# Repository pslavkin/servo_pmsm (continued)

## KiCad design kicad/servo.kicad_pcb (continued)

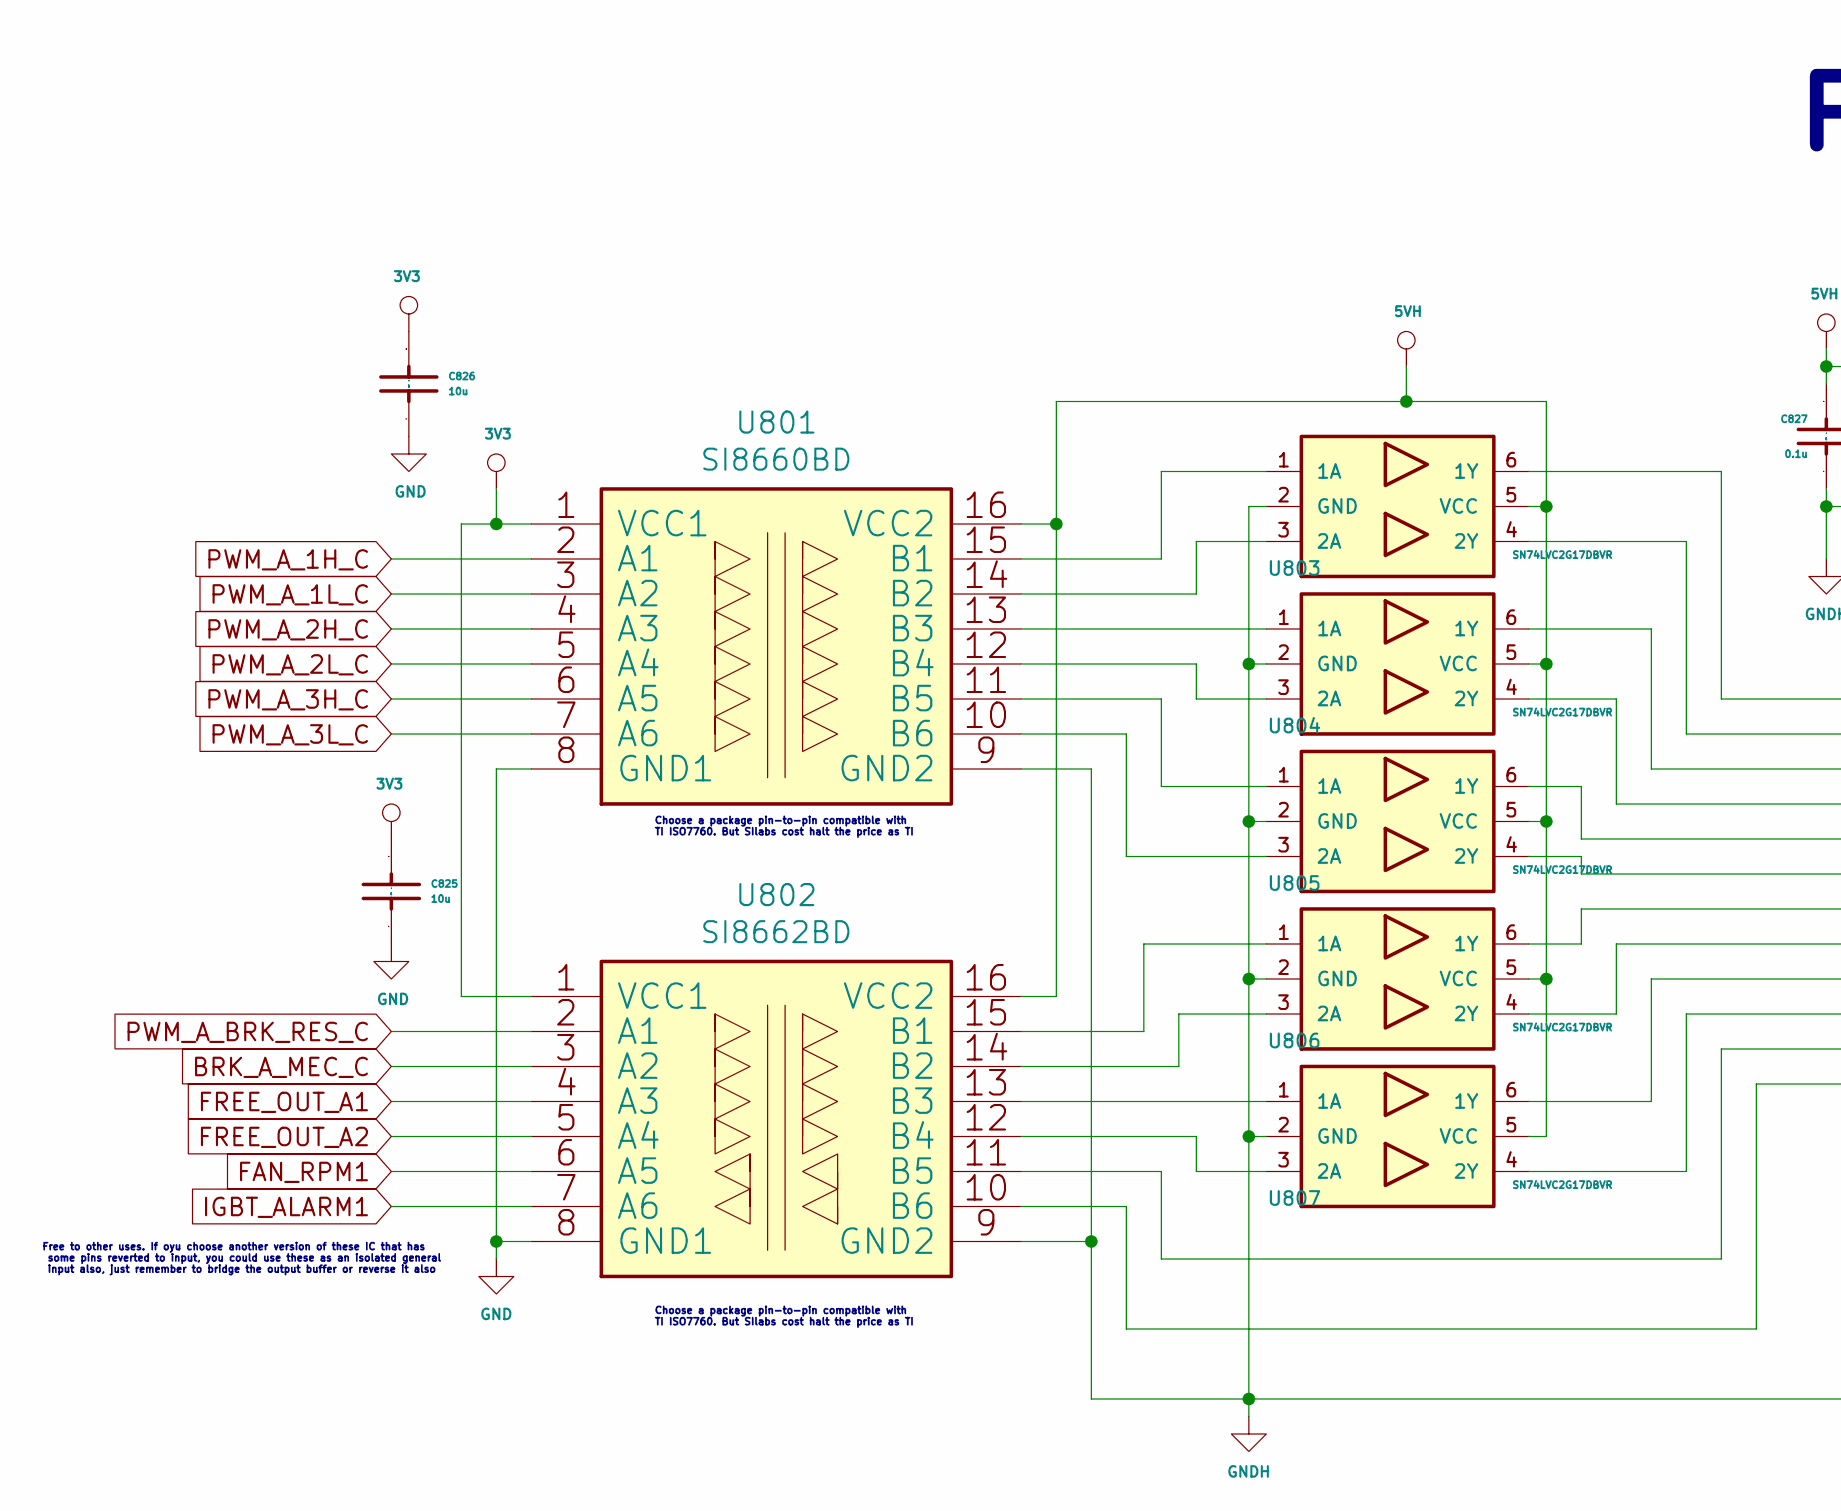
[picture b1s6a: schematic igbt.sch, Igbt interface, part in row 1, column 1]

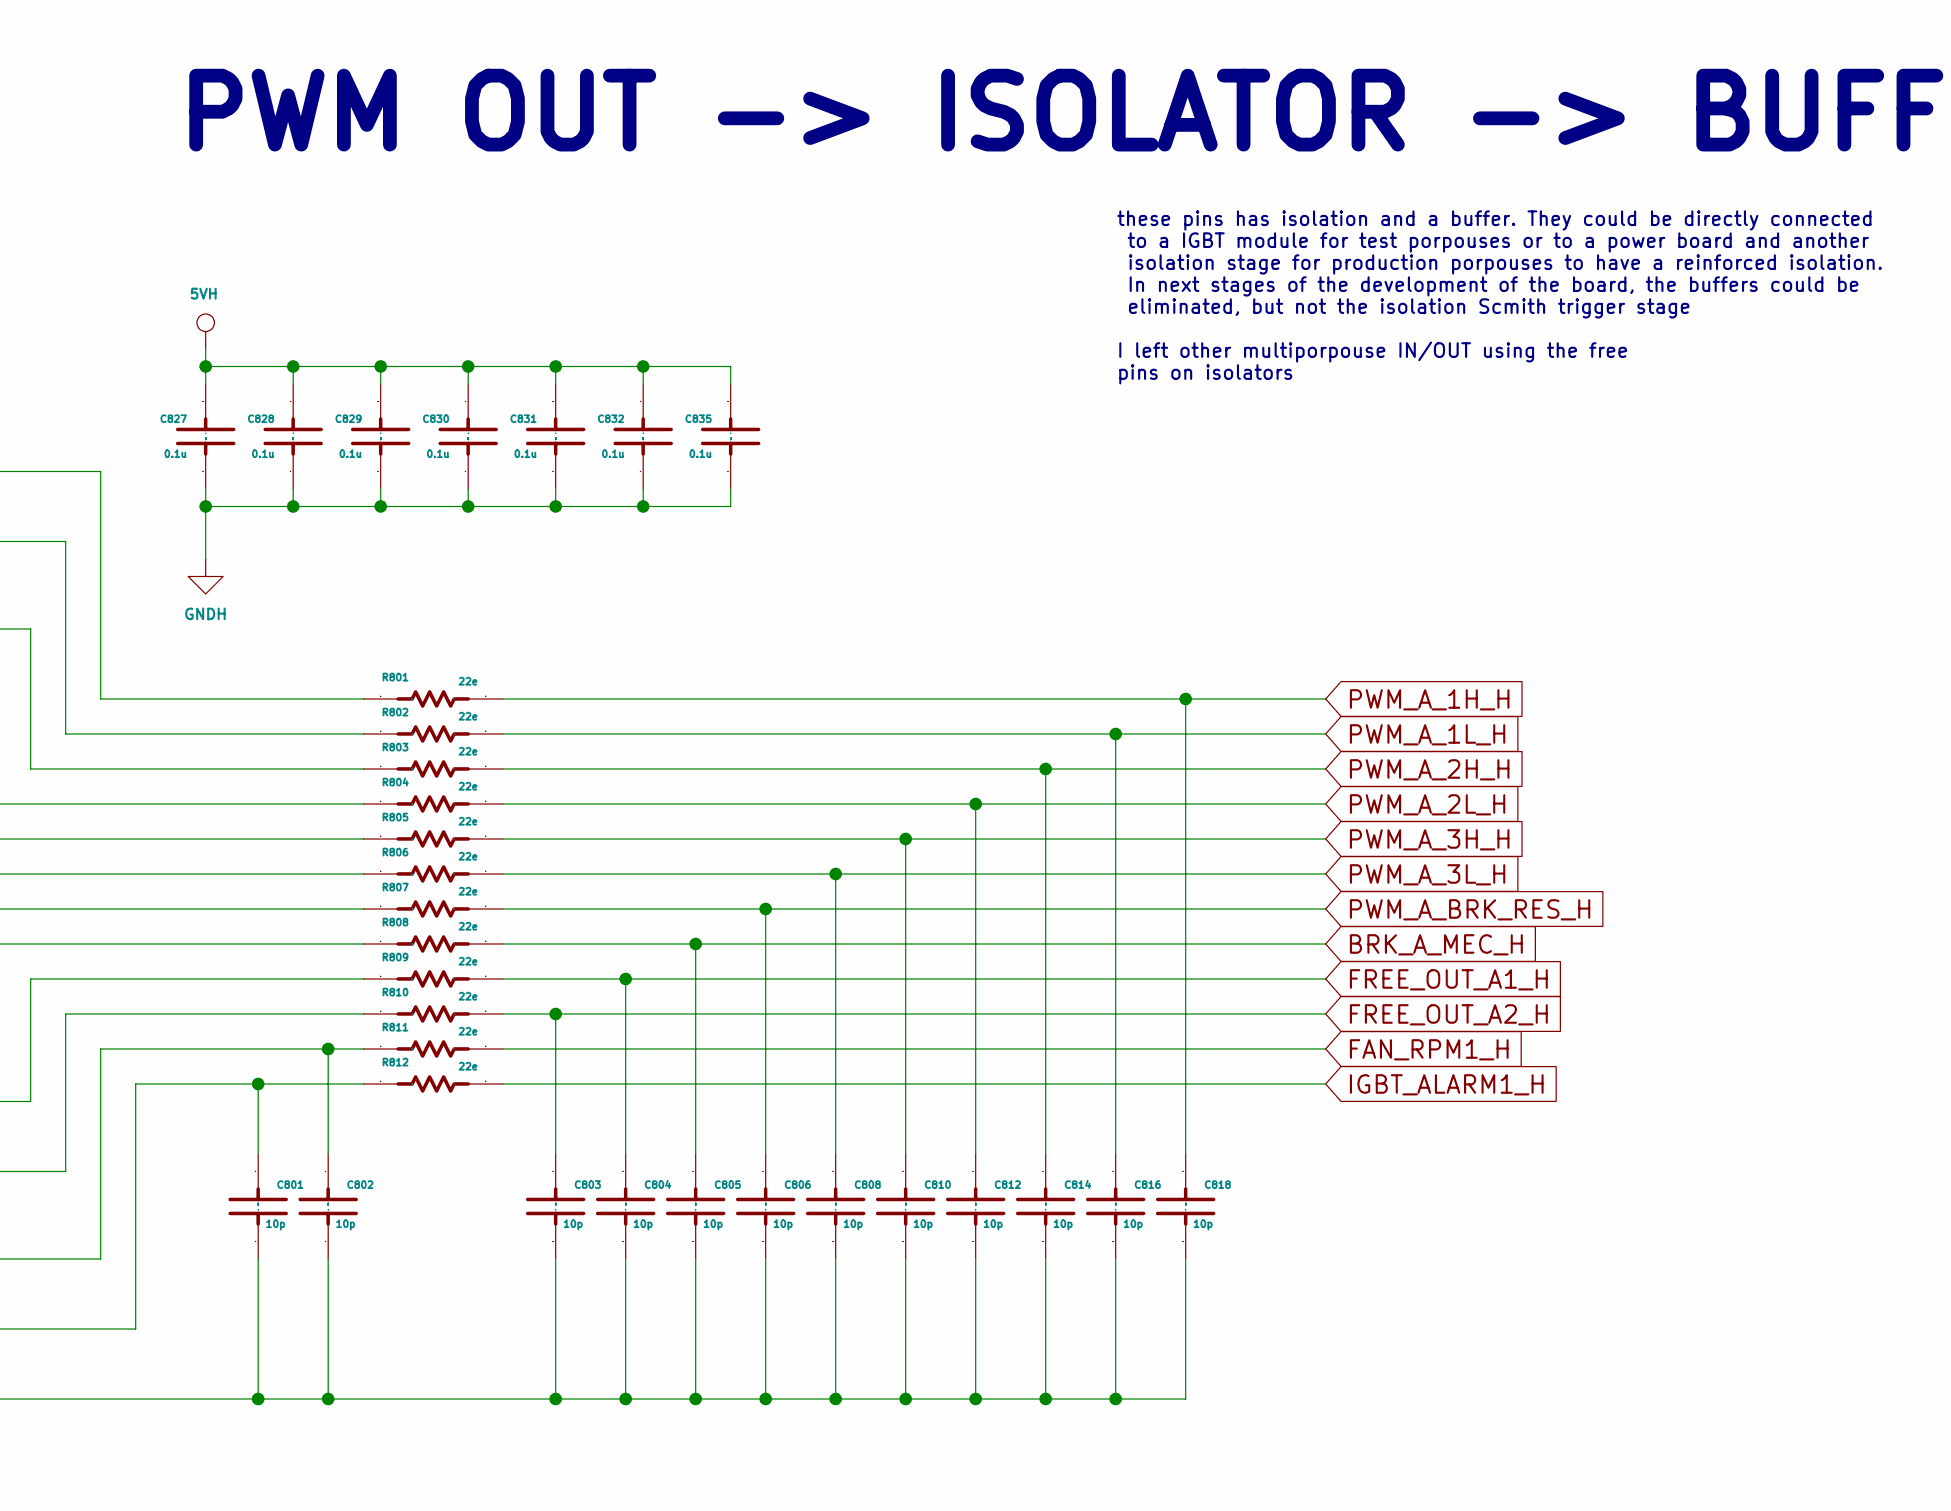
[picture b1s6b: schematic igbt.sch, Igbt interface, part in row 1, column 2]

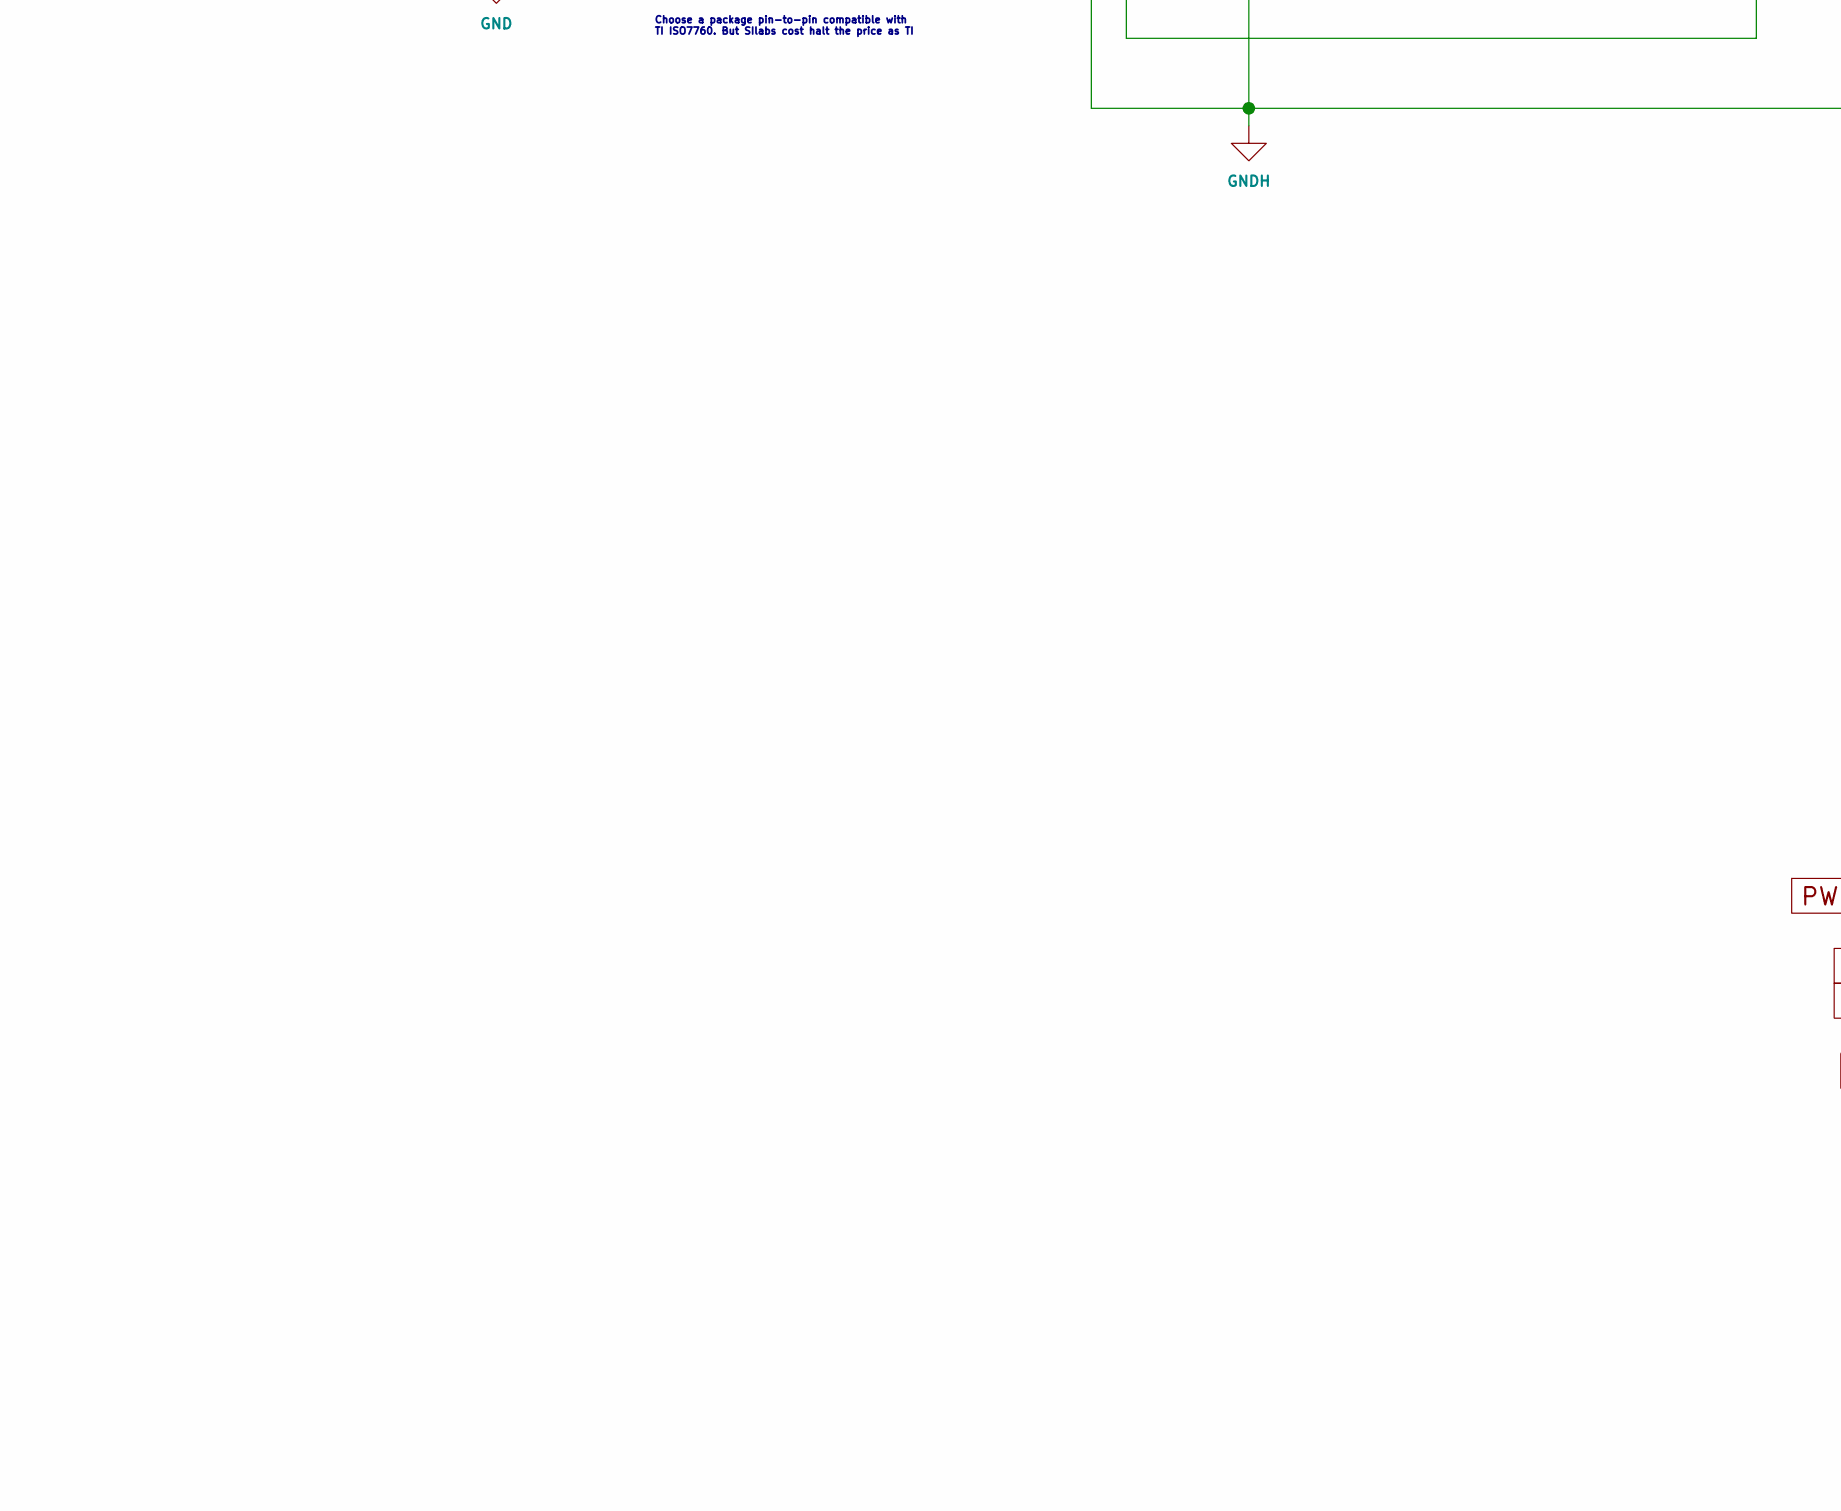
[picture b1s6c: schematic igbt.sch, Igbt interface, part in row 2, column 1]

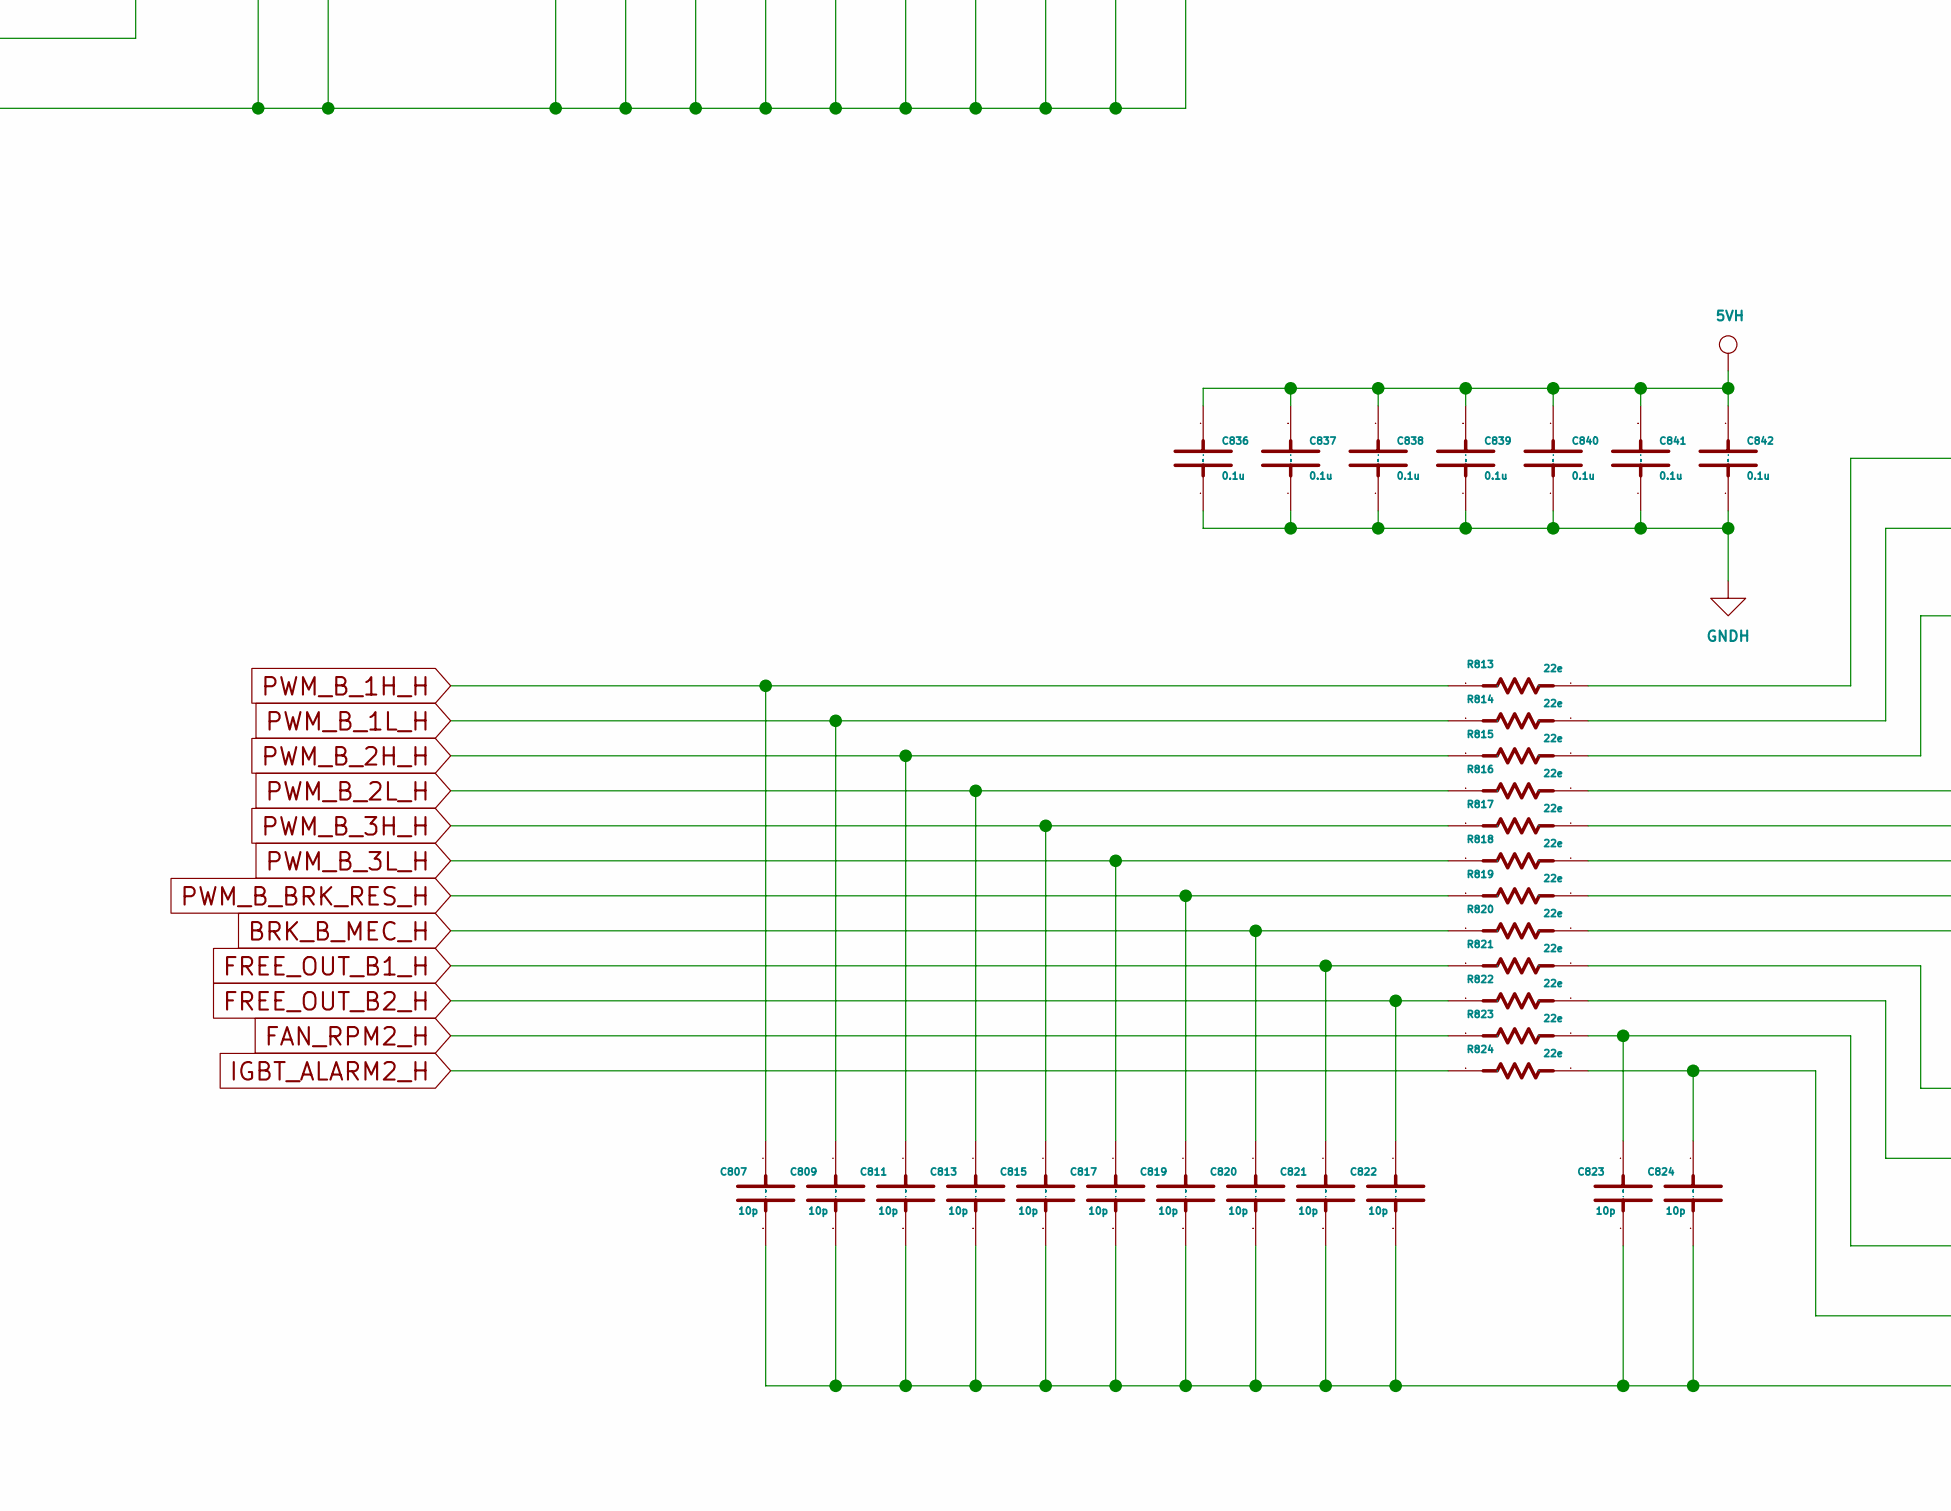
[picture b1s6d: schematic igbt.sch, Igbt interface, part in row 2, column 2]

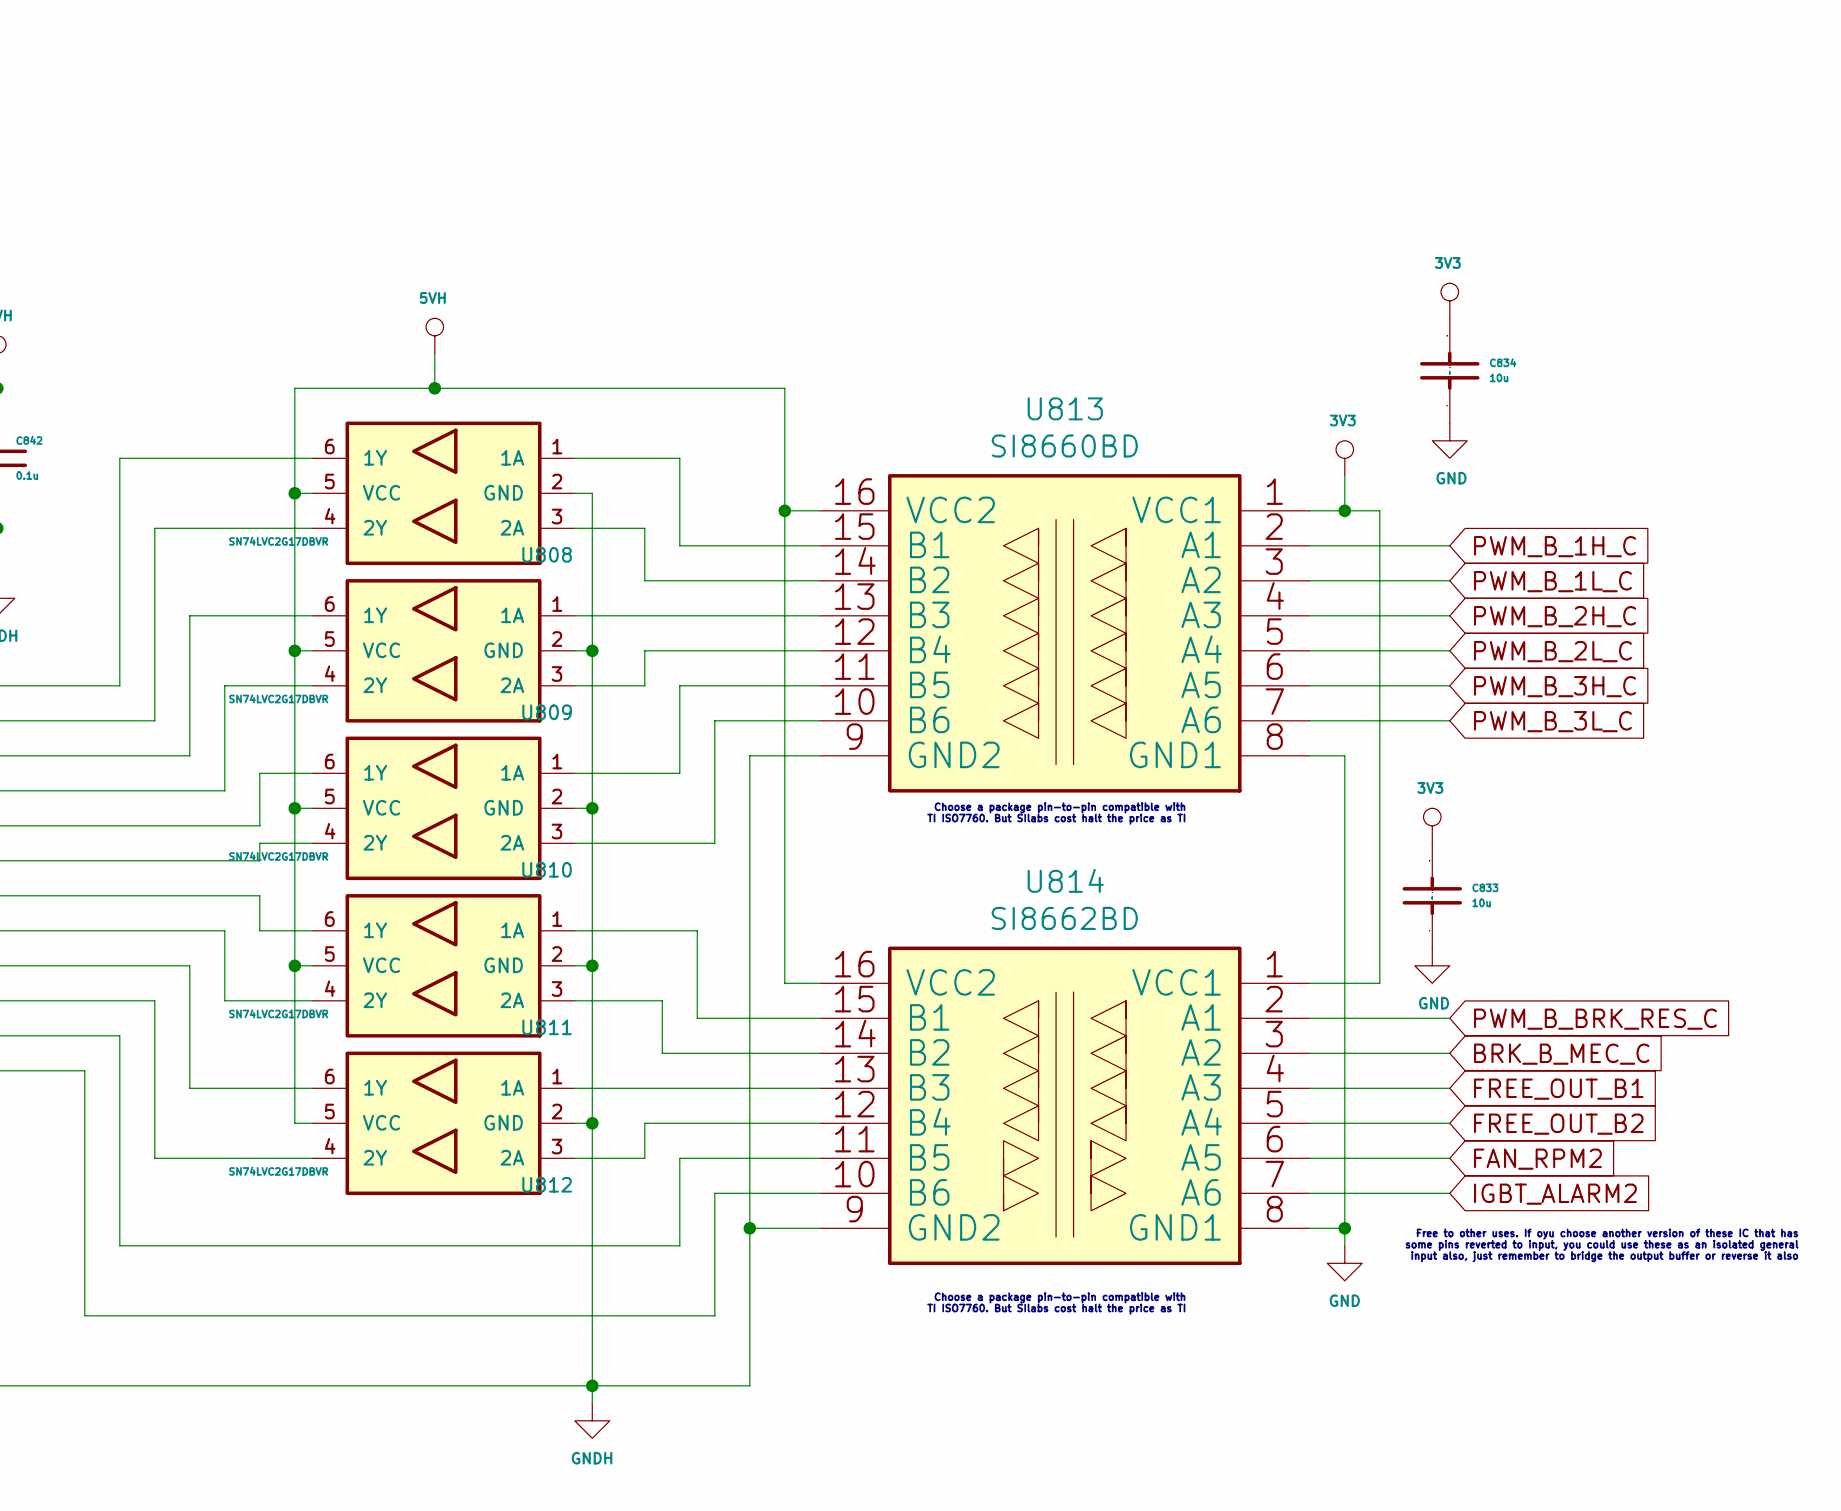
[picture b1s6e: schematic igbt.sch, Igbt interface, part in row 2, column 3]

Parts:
C801, C802, C803, C804, C805, C806, C807, C808, C809, C810, C811, C812, C813, C814, C815, C816, C817, C818, C819, C820, C821, C822, C823, C824: 10p; C_0603_1608Metric
C825, C826, C833, C834: 10u; C_0603_1608Metric
C827, C828, C829, C830, C831, C832, C835, C836, C837, C838, C839, C840, C841, C842: 0.1u; C_0603_1608Metric
R801, R802, R803, R804, R805, R806, R807, R808, R809, R810, R811, R812, R813, R814, R815, R816, R817, R818, R819, R820, R821, R822, R823, R824: 22e; R_0603_1608Metric
U801, U813: SI8660BD; SOIC-16W_7.5x10.3mm_P1.27mm
U802, U814: SI8662BD; SOIC-16W_7.5x10.3mm_P1.27mm
U803, U804, U805, U806, U807, U808, U809, U810, U811, U812: SN74LVC2G17DBVR; SOT-23-6

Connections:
3V3: C825.1, C826.1, C833.1, C834.1, U801.1 (VCC1), U802.1 (VCC1), U813.1 (VCC1), U814.1 (VCC1); also elsewhere on the board
5VH: C827.1, C828.1, C829.1, C830.1, C831.1, C832.1, C835.1, C836.1, C837.1, C838.1, C839.1, C840.1, C841.1, C842.1, U801.16 (VCC2), U802.16 (VCC2), U803.5 (VCC), U804.5 (VCC), U805.5 (VCC), U806.5 (VCC), U807.5 (VCC), U808.5 (VCC), U809.5 (VCC), U810.5 (VCC), U811.5 (VCC), U812.5 (VCC), U813.16 (VCC2), U814.16 (VCC2); also elsewhere on the board
BRK_A_MEC_C: U802.3 (A2); also elsewhere on the board
BRK_A_MEC_H: C805.2 (Capacitor), R808.2; also elsewhere on the board
BRK_B_MEC_C: U814.3 (A2); also elsewhere on the board
BRK_B_MEC_H: C820.2 (Capacitor), R820.1; also elsewhere on the board
FAN_RPM1: U802.6 (A5); also elsewhere on the board
FAN_RPM1_H: R811.2; also elsewhere on the board
FAN_RPM2: U814.6 (A5); also elsewhere on the board
FAN_RPM2_H: R823.1; also elsewhere on the board
FREE_OUT_A1: U802.4 (A3); also elsewhere on the board
FREE_OUT_A1_H: C804.2 (Capacitor), R809.2; also elsewhere on the board
FREE_OUT_A2: U802.5 (A4); also elsewhere on the board
FREE_OUT_A2_H: C803.2 (Capacitor), R810.2; also elsewhere on the board
FREE_OUT_B1: U814.4 (A3); also elsewhere on the board
FREE_OUT_B1_H: C821.2 (Capacitor), R821.1; also elsewhere on the board
FREE_OUT_B2: U814.5 (A4); also elsewhere on the board
FREE_OUT_B2_H: C822.2 (Capacitor), R822.1; also elsewhere on the board
GND: C825.2 (Capacitor), C826.2 (Capacitor), C833.2 (Capacitor), C834.2 (Capacitor), U801.8 (GND1), U802.8 (GND1), U813.8 (GND1), U814.8 (GND1); also elsewhere on the board
GNDH: C801.1, C802.1, C803.1, C804.1, C805.1, C806.1, C807.1, C808.1, C809.1, C810.1, C811.1, C812.1, C813.1, C814.1, C815.1, C816.1, C817.1, C818.1, C819.1, C820.1, C821.1, C822.1, C823.1, C824.1, C827.2 (Capacitor), C828.2 (Capacitor), C829.2 (Capacitor), C830.2 (Capacitor), C831.2 (Capacitor), C832.2 (Capacitor), C835.2 (Capacitor), C836.2 (Capacitor), C837.2 (Capacitor), C838.2 (Capacitor), C839.2 (Capacitor), C840.2 (Capacitor), C841.2 (Capacitor), C842.2 (Capacitor), U801.9 (GND2), U802.9 (GND2), U803.2 (GND), U804.2 (GND), U805.2 (GND), U806.2 (GND), U807.2 (GND), U808.2 (GND), U809.2 (GND), U810.2 (GND), U811.2 (GND), U812.2 (GND), U813.9 (GND2), U814.9 (GND2); also elsewhere on the board
IGBT_ALARM1: U802.7 (A6); also elsewhere on the board
IGBT_ALARM1_H: R812.2; also elsewhere on the board
IGBT_ALARM2: U814.7 (A6); also elsewhere on the board
IGBT_ALARM2_H: R824.1; also elsewhere on the board
unnamed: C801.2 (Capacitor), R812.1, U802.10 (B6)
unnamed: C802.2 (Capacitor), R811.1, U802.11 (B5)
unnamed: C823.2 (Capacitor), R823.2, U814.11 (B5)
unnamed: C824.2 (Capacitor), R824.2, U814.10 (B6)
unnamed: R801.1, U803.6 (1Y)
unnamed: R802.1, U803.4 (2Y)
unnamed: R803.1, U804.6 (1Y)
unnamed: R804.1, U804.4 (2Y)
unnamed: R805.1, U805.6 (1Y)
unnamed: R806.1, U805.4 (2Y)
unnamed: R807.1, U806.6 (1Y)
unnamed: R808.1, U806.4 (2Y)
unnamed: R809.1, U807.6 (1Y)
unnamed: R810.1, U807.4 (2Y)
unnamed: R813.2, U808.6 (1Y)
unnamed: R814.2, U808.4 (2Y)
unnamed: R815.2, U809.6 (1Y)
unnamed: R816.2, U809.4 (2Y)
unnamed: R817.2, U810.6 (1Y)
unnamed: R818.2, U810.4 (2Y)
unnamed: R819.2, U811.6 (1Y)
unnamed: R820.2, U811.4 (2Y)
unnamed: R821.2, U812.6 (1Y)
unnamed: R822.2, U812.4 (2Y)
unnamed: U801.10 (B6), U805.3 (2A)
unnamed: U801.11 (B5), U805.1 (1A)
unnamed: U801.12 (B4), U804.3 (2A)
unnamed: U801.13 (B3), U804.1 (1A)
unnamed: U801.14 (B2), U803.3 (2A)
unnamed: U801.15 (B1), U803.1 (1A)
unnamed: U802.12 (B4), U807.3 (2A)
unnamed: U802.13 (B3), U807.1 (1A)
unnamed: U802.14 (B2), U806.3 (2A)
unnamed: U802.15 (B1), U806.1 (1A)
unnamed: U808.1 (1A), U813.15 (B1)
unnamed: U808.3 (2A), U813.14 (B2)
unnamed: U809.1 (1A), U813.13 (B3)
unnamed: U809.3 (2A), U813.12 (B4)
unnamed: U810.1 (1A), U813.11 (B5)
unnamed: U810.3 (2A), U813.10 (B6)
unnamed: U811.1 (1A), U814.15 (B1)
unnamed: U811.3 (2A), U814.14 (B2)
unnamed: U812.1 (1A), U814.13 (B3)
unnamed: U812.3 (2A), U814.12 (B4)
PWM_A_1H_C: U801.2 (A1); also elsewhere on the board
PWM_A_1H_H: C818.2 (Capacitor), R801.2; also elsewhere on the board
PWM_A_1L_C: U801.3 (A2); also elsewhere on the board
PWM_A_1L_H: C816.2 (Capacitor), R802.2; also elsewhere on the board
PWM_A_2H_C: U801.4 (A3); also elsewhere on the board
PWM_A_2H_H: C814.2 (Capacitor), R803.2; also elsewhere on the board
PWM_A_2L_C: U801.5 (A4); also elsewhere on the board
PWM_A_2L_H: C812.2 (Capacitor), R804.2; also elsewhere on the board
PWM_A_3H_C: U801.6 (A5); also elsewhere on the board
PWM_A_3H_H: C810.2 (Capacitor), R805.2; also elsewhere on the board
PWM_A_3L_C: U801.7 (A6); also elsewhere on the board
PWM_A_3L_H: C808.2 (Capacitor), R806.2; also elsewhere on the board
PWM_A_BRK_RES_C: U802.2 (A1); also elsewhere on the board
PWM_A_BRK_RES_H: C806.2 (Capacitor), R807.2; also elsewhere on the board
PWM_B_1H_C: U813.2 (A1); also elsewhere on the board
PWM_B_1H_H: C807.2 (Capacitor), R813.1; also elsewhere on the board
PWM_B_1L_C: U813.3 (A2); also elsewhere on the board
PWM_B_1L_H: C809.2 (Capacitor), R814.1; also elsewhere on the board
PWM_B_2H_C: U813.4 (A3); also elsewhere on the board
PWM_B_2H_H: C811.2 (Capacitor), R815.1; also elsewhere on the board
PWM_B_2L_C: U813.5 (A4); also elsewhere on the board
PWM_B_2L_H: C813.2 (Capacitor), R816.1; also elsewhere on the board
PWM_B_3H_C: U813.6 (A5); also elsewhere on the board
PWM_B_3H_H: C815.2 (Capacitor), R817.1; also elsewhere on the board
PWM_B_3L_C: U813.7 (A6); also elsewhere on the board
PWM_B_3L_H: C817.2 (Capacitor), R818.1; also elsewhere on the board
PWM_B_BRK_RES_C: U814.2 (A1); also elsewhere on the board
PWM_B_BRK_RES_H: C819.2 (Capacitor), R819.1; also elsewhere on the board

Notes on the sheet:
PWM OUT -> ISOLATOR -> BUFFER -> FILTER
these pins has isolation and a buffer. They could be directly connected to a IGBT module for test porpouses or to a power board and another isolation stage for production porpouses to have a reinforced isolation. In next stages of the development of the board, the buffers could be eliminated, but n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
Choose a package pin-to-pin compatible with TI ISO7760. But SIlabs cost halt the price as TI
Free to other uses. If oyu choose another version of these IC that has some pins reverted to input, you could use these as an isolated general input also, just remember to bridge the output buffer or reverse it also
